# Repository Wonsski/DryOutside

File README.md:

# DryOutside
ESP32 based device for weather monitoring

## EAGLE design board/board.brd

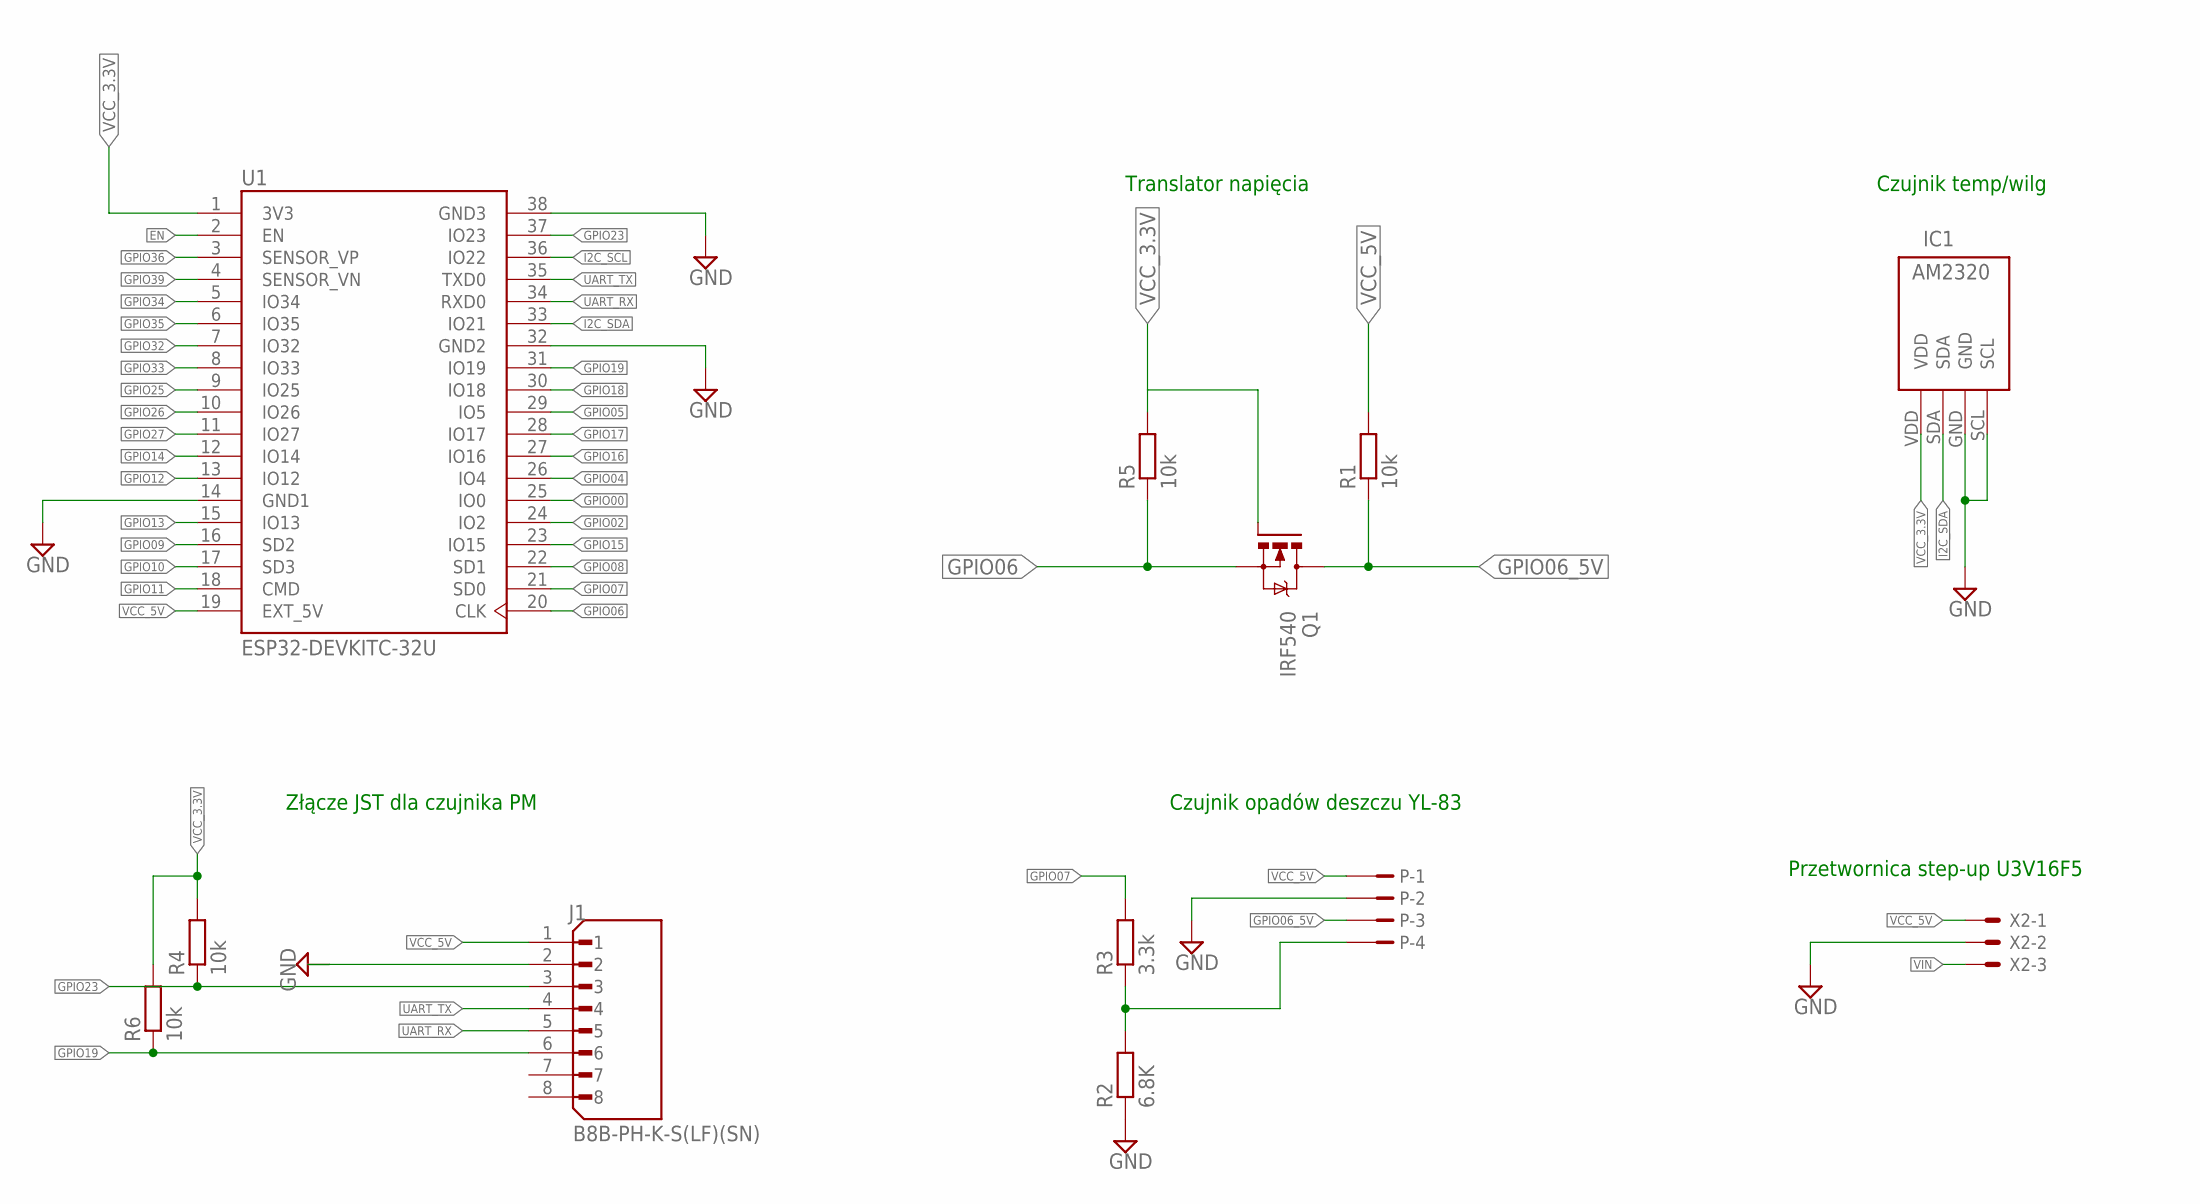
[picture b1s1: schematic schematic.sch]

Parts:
IC1: AM2320
J1: B8B-PH-K-S(LF)(SN); JST_B8B-PH-K-S(LF)(SN)
P: B4B-ZR
Q1: IRF540; TO220BV
R1, R4, R5, R6: 10k; 0204V
R2: 6.8K; 0204V
R3: 3.3k; 0204V
U1: ESP32-DEVKITC-32U; MODULE_ESP32-DEVKITC-32U
X2: 22-23-2031

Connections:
EN: U1.2 (EN)
GND: IC1.GND, IC1.SCL, J1.2, P.2, R2.1, U1.14 (GND1), U1.32 (GND2), U1.38 (GND3), X2.2
GPIO00: U1.25 (IO0)
GPIO02: U1.24 (IO2)
GPIO04: U1.26 (IO4)
GPIO05: U1.29 (IO5)
GPIO06: Q1.S, R5.1, U1.20 (CLK)
GPIO06_5V: P.3, Q1.D, R1.1
GPIO07: R3.2, U1.21 (SD0)
GPIO08: U1.22 (SD1)
GPIO09: U1.16 (SD2)
GPIO10: U1.17 (SD3)
GPIO11: U1.18 (CMD)
GPIO12: U1.13 (IO12)
GPIO13: U1.15 (IO13)
GPIO14: U1.12 (IO14)
GPIO15: U1.23 (IO15)
GPIO16: U1.27 (IO16)
GPIO17: U1.28 (IO17)
GPIO18: U1.30 (IO18)
GPIO19: J1.6, R6.1, U1.31 (IO19)
GPIO23: J1.3, R4.1, U1.37 (IO23)
GPIO25: U1.9 (IO25)
GPIO26: U1.10 (IO26)
GPIO27: U1.11 (IO27)
GPIO32: U1.7 (IO32)
GPIO33: U1.8 (IO33)
GPIO34: U1.5 (IO34)
GPIO35: U1.6 (IO35)
GPIO36: U1.3 (SENSOR_VP)
GPIO39: U1.4 (SENSOR_VN)
I2C_SCL: U1.36 (IO22)
I2C_SDA: IC1.SDA, U1.33 (IO21)
unnamed: P.4, R2.2, R3.1
UART_RX: J1.5, U1.34 (RXD0)
UART_TX: J1.4, U1.35 (TXD0)
VCC_3.3V: IC1.VDD, Q1.G, R4.2, R5.2, R6.2, U1.1 (3V3)
VCC_5V: J1.1, P.1, R1.2, U1.19 (EXT_5V), X2.1
VIN: X2.3

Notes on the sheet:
Czujnik temp/wilg
Translator napięcia
Złącze JST dla czujnika PM
Przetwornica step-up U3V16F5
Czujnik opadów deszczu YL-83

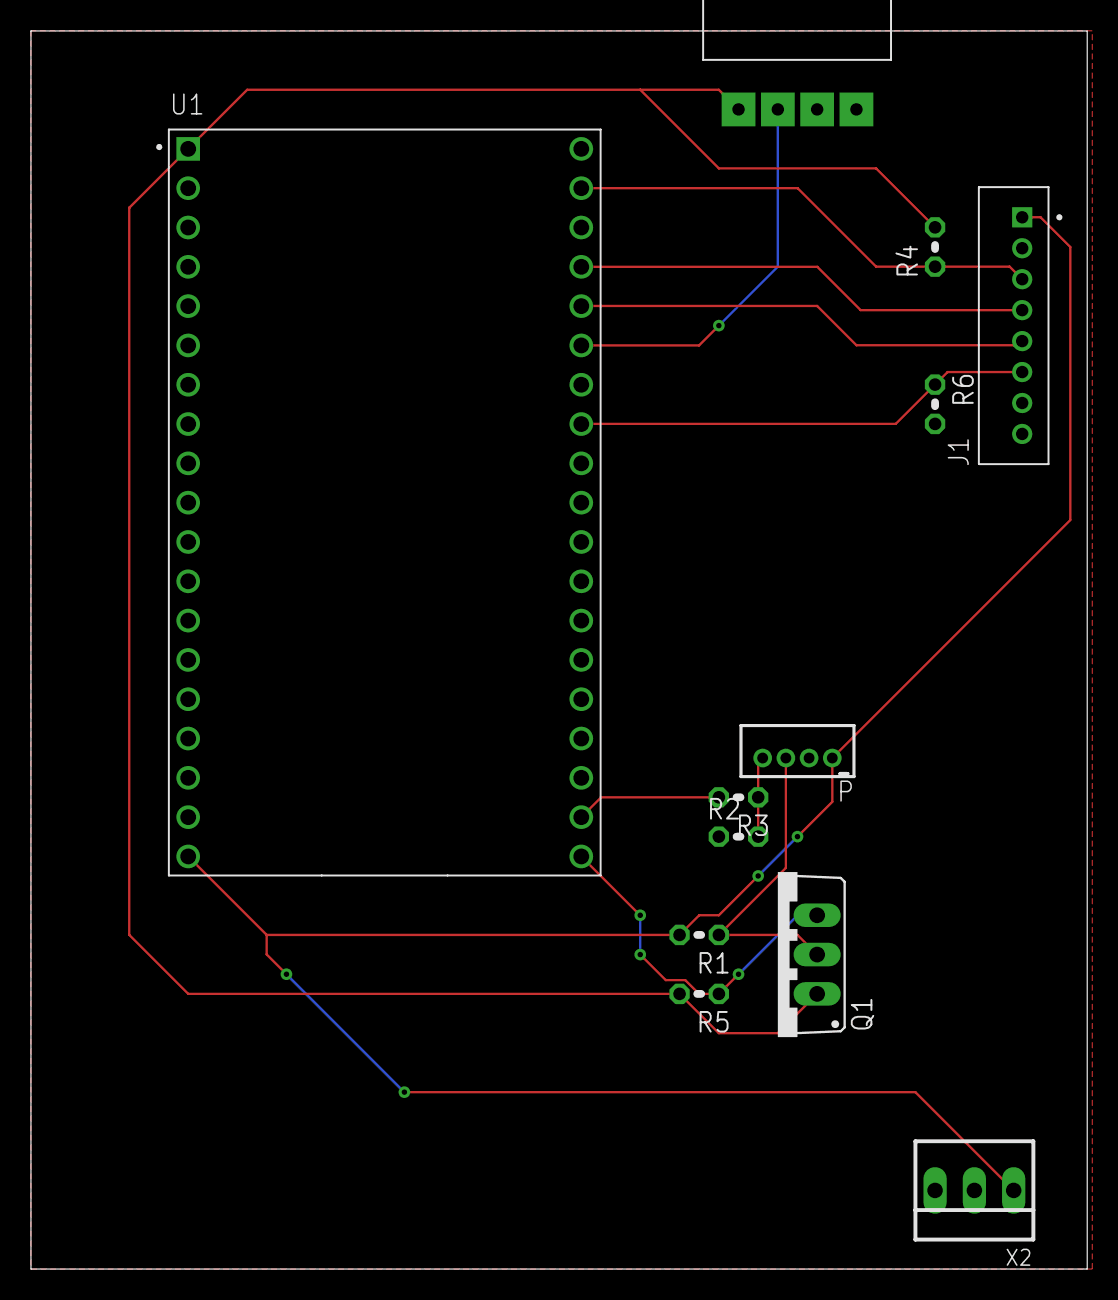
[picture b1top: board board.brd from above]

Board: 2 copper layers, 68.2 x 80.0 mm, 12 parts (0 on the bottom side), 12 nets.

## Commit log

2024-11-29 Add sensor test for PM sensor
2024-11-29 DHT22 sensor support. Created main loop
2024-12-14 Implement Web user interface with data logging
2025-02-04 Upload project assets
